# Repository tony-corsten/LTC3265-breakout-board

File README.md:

# LTC3265-breakout-board
# Overview
The LTC3265 is a compact, low-noise, potentially quad rail supply utilizing a charge-pump architecture with input voltage from 4V - 16V and output voltages of approximately -32V - 32V (total output current of 50mV). The main difference between the LTC3265 and the LTC3260 is that the LTC3265 has a boost regulator on the input, making it ideal for high voltage supplies (e.g., +/- 15V from a 9V input). The chip can have up to four outputs: 1) a doubled input voltage output, 2) an inverted output (either from the input or doubled input voltage), 3) & 4) a positive and negative LDO. This makes it extremely versatile for boards that require either very low noise dual rails for op amps, or multiple dual rails for high-powered devices that are more noise tolerant. [You can find the official documentation for the chip here](https://www.analog.com/en/products/ltc3265.html). This is a breakout board made in Kicad with a barrel jack power input [(the PJ-037A)](https://www.digikey.com/product-detail/en/cui-inc/PJ-037A/CP-037A-ND/1644545) and 2.54mm through holes for output voltages (your choice of header pins or a screw terminal block!)

*_Note_*: The board is currently designed for a +/- 15V rail for a 9V battery input. You can adjust the output voltage by tweaking the setting resistors, RLDOP1/2 and RDLON1/2. The ratio is described on pages 12/13 of the technical manual. 

# Navigating this repo
The main folder contains relevant Kicad files (.pro, .pcb, .sch). The `gerber` directory has a PCB-fabrication ready set of gerber files. The `library` directory contains a custom kicad footprint for the PJ-037A. 

# Board images
PCB Layout:

Schematic:

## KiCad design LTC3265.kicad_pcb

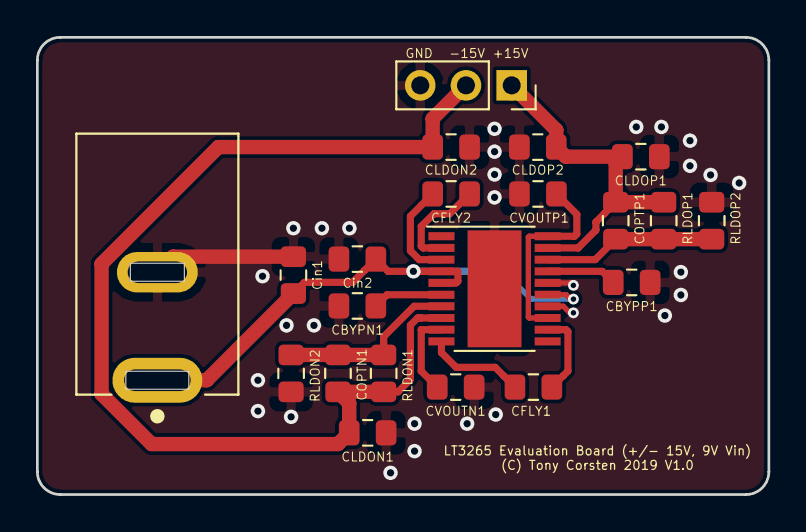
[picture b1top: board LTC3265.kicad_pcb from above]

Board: 2 copper layers, 40.6 x 25.4 mm, 21 parts (0 on the bottom side), 14 nets.

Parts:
CBYPN1: 0.1uF; C_0805_2012Metric_Pad1.15x1.40mm_HandSolder
CBYPP1: 0.1uF; C_0805_2012Metric_Pad1.15x1.40mm_HandSolder
CFLY1, CFLY2: 1uF; C_0805_2012Metric_Pad1.15x1.40mm_HandSolder
CLDON1: 2uF; C_0805_2012Metric_Pad1.15x1.40mm_HandSolder
CLDON2: 0.1uF; C_0805_2012Metric_Pad1.15x1.40mm_HandSolder
CLDOP1: 2uF; C_0805_2012Metric_Pad1.15x1.40mm_HandSolder
CLDOP2: 0.1uF; C_0805_2012Metric_Pad1.15x1.40mm_HandSolder
COPTN1: 10pF; C_0805_2012Metric_Pad1.15x1.40mm_HandSolder
COPTP1: 10pF; C_0805_2012Metric_Pad1.15x1.40mm_HandSolder
CVOUTN1: 10uF; C_0805_2012Metric_Pad1.15x1.40mm_HandSolder
CVOUTP1: 10uF; C_0805_2012Metric_Pad1.15x1.40mm_HandSolder
Cin1: 10uF; C_0805_2012Metric_Pad1.15x1.40mm_HandSolder
Cin2: 0.1uF; C_0805_2012Metric_Pad1.15x1.40mm_HandSolder
J1: Barrel_Jack; PJ-037A
J2: Conn_01x03_Male; PinSocket_1x03_P2.54mm_Vertical
RLDON1: 604k; R_0805_2012Metric_Pad1.15x1.40mm_HandSolder
RLDON2: 52.3k; R_0805_2012Metric_Pad1.15x1.40mm_HandSolder
RLDOP1: 604k; R_0805_2012Metric_Pad1.15x1.40mm_HandSolder
RLDOP2: 52.3k; R_0805_2012Metric_Pad1.15x1.40mm_HandSolder
U1: LTC3265EFE; HTSSOP-20-1EP_4.4x6.5mm_P0.65mm_EP3x6.5mm

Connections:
+9V: Cin1.1, Cin2.1, J1.1, U1.4, U1.5, U1.15
/+15V: CLDOP1.1, CLDOP2.1, COPTP1.2, J2.1, RLDOP1.1, U1.19
/-15V: CLDON1.2, CLDON2.1, COPTN1.1, J2.2, RLDON1.2, U1.8
/ADJ+: COPTP1.1, RLDOP1.2, RLDOP2.2, U1.18
/ADJ-: COPTN1.2, RLDON1.1, RLDON2.2, U1.7
/BYP+: CBYPP1.2, U1.17
/BYP-: CBYPN1.2, U1.6
/VOUT+: CVOUTP1.2, U1.13, U1.20
GND: CBYPN1.1, CBYPP1.1, CLDON1.1, CLDON2.2, CLDOP1.2, CLDOP2.2, CVOUTN1.2, CVOUTP1.1, Cin1.2, Cin2.2, J1.2, J2.3, RLDON2.1, RLDOP2.1, U1.14, U1.16, U1.21
unnamed: CFLY1.1, U1.10
unnamed: CFLY1.2, U1.12
unnamed: CFLY2.1, U1.2
unnamed: CFLY2.2, U1.3
unnamed: CVOUTN1.1, U1.9

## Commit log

2019-08-18 adding schematic file, library directory
